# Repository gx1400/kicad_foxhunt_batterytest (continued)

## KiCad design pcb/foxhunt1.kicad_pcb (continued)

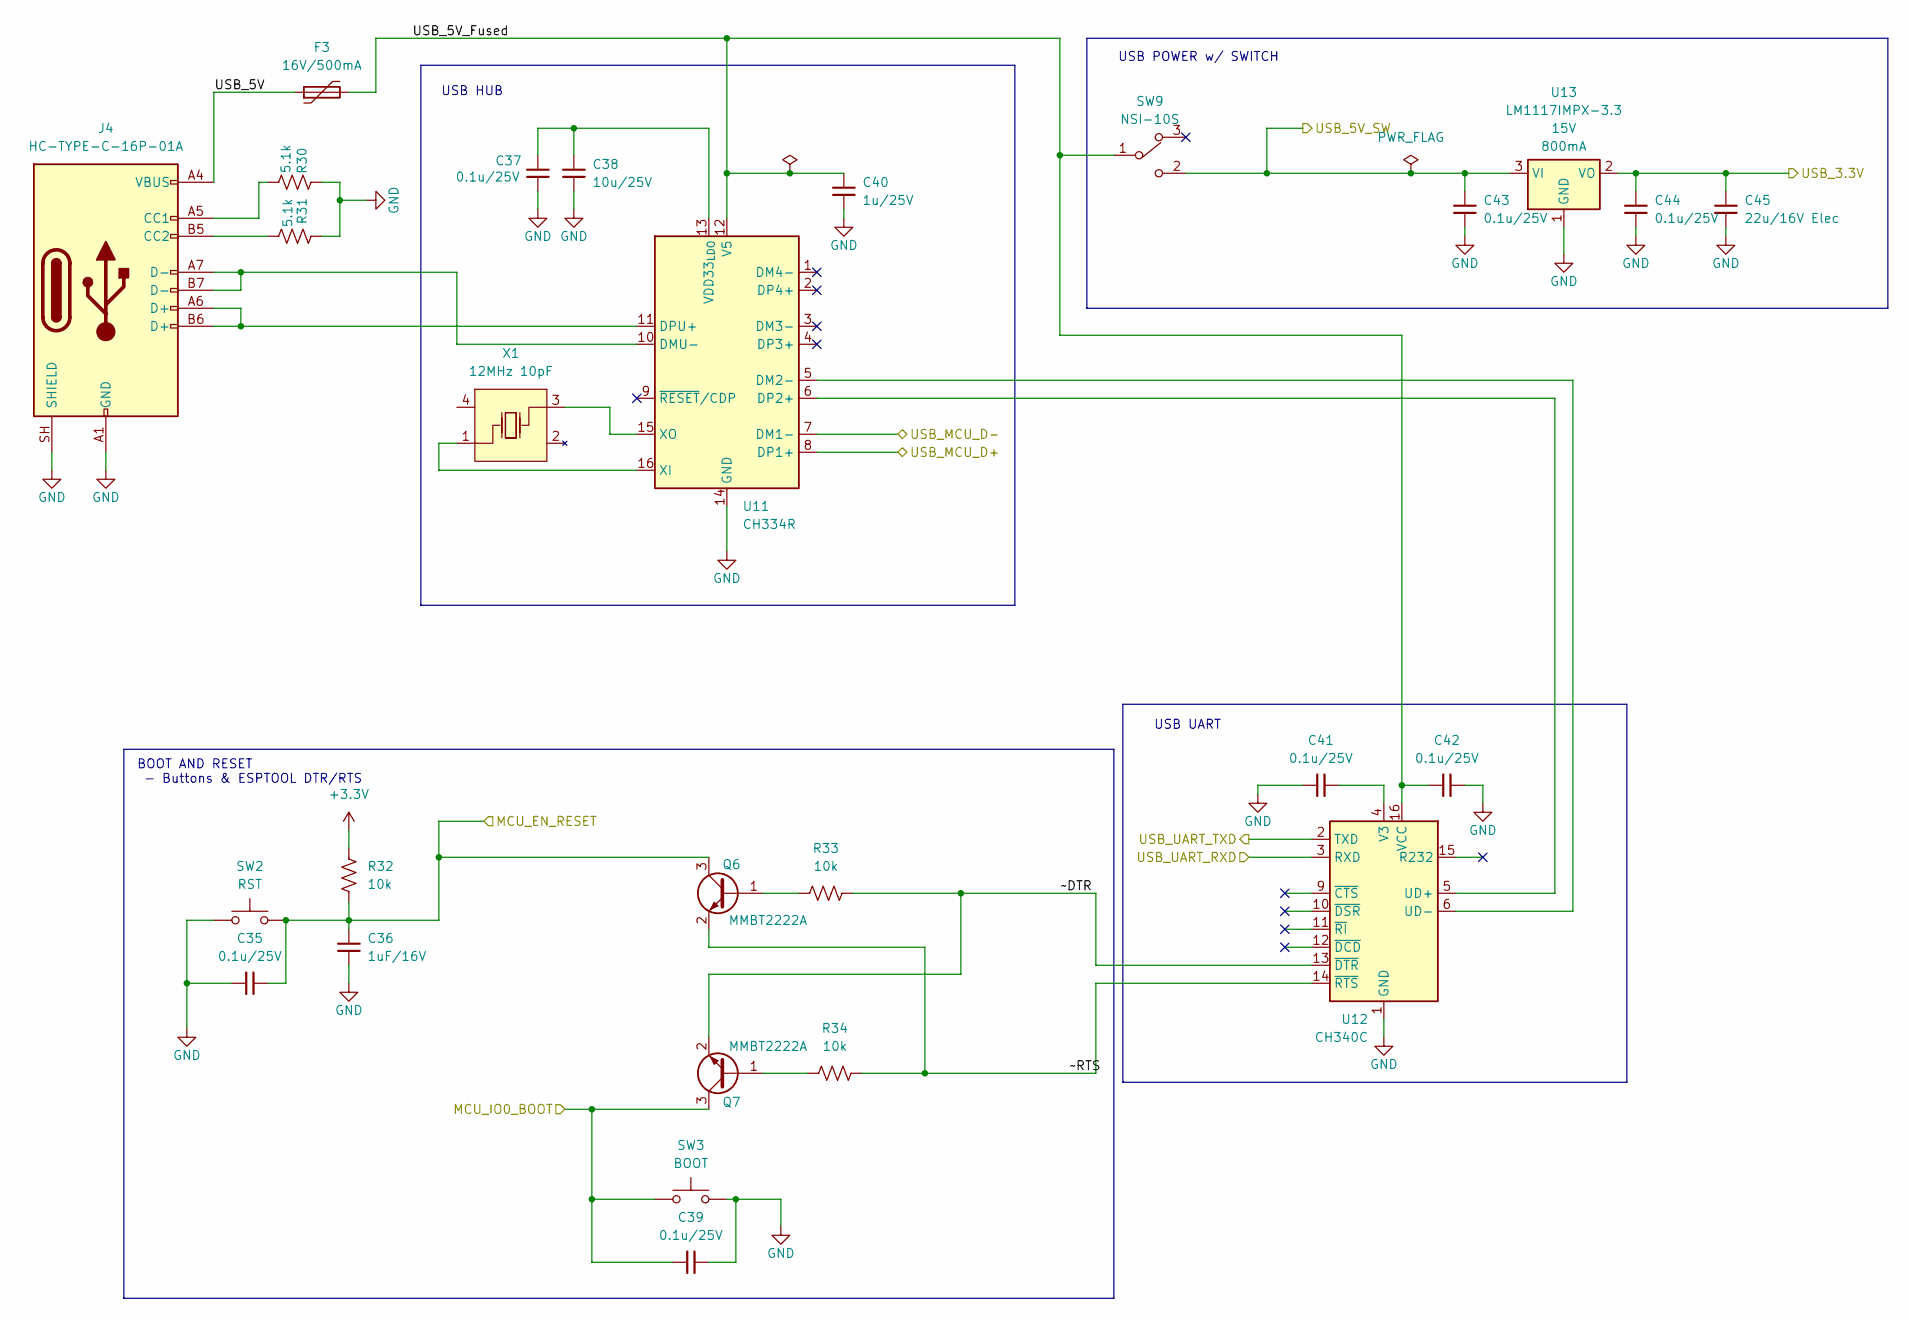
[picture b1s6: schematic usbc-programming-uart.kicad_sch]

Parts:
C35, C37, C39, C41, C42, C43, C44: 0.1u/25V; C_0603_1608Metric; MPN GRM188R71H104KA93D; LCSC Part # C77055
C36: 1uF/16V; C_0805_2012Metric; MPN GRM21BR71H105KA12L; LCSC Part # C77083
C38: 10u/25V; C_0805_2012Metric; MPN GRM21BZ71E106KE15L; LCSC Part # C237493
C40: 1u/25V; C_0805_2012Metric; MPN GRM21BR71H105KA12L; LCSC Part # C77083
C45: 22u/16V Elec; C_Elec_5x5.8; MPN XT1C220M0506; LCSC Part # C5260805
F3: 16V/500mA; Fuse_0805_2012Metric; MPN 0805L050/16XR; LCSC Part # C22435898
J4: HC-TYPE-C-16P-01A; USB_C_Receptacle_HCTL_HC-TYPE-C-16P-01A; MPN HC-TYPE-C-16P-01A; LCSC Part # C2894897
Q6, Q7: MMBT2222A; SOT-23; MPN MMBT2222ALT1G; LCSC Part # C82460
R30, R31: 5.1k; R_0603_1608Metric; MPN RC0603JR-075K1L; LCSC Part # C14677
R32, R33, R34: 10k; R_0603_1608Metric; MPN RT0603BRD0710KL; LCSC Part # C95204
SW2: RST; SW_SPST_PTS645Sx43SMTR92; MPN K2-1102SP-A4SC-04; LCSC Part # C83916
SW3: BOOT; SW_SPST_PTS645Sx43SMTR92; MPN K2-1102SP-A4SC-04; LCSC Part # C83916
SW9: NSI-10S; SW-SMD_NSI-10S; MPN NSI-10S; LCSC Part C515802
U11: CH334R; QSOP-16_3.9x4.9mm_P0.635mm; MPN CH334R; LCSC Part # C4154405
U12: CH340C; SOIC-16_3.9x9.9mm_P1.27mm; MPN CH340C; LCSC Part # C84681
U13: LM1117IMPX-3.3; SOT-223-3_TabPin2; MPN LM1117IMPX-3.3/NOPB; LCSC Part # C23984
X1: 12MHz 10pF; CRYSTAL-SMD_4P-L2.5-W2.0-BL; MPN TXM12M0004252DBCEO00T; LCSC Part # C284154

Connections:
+3.3V: R32.2; also elsewhere on the board
/Power/USB_3.3V_IN: C44.1, C45.1, U13.2 (VO); also elsewhere on the board
/Power/USB_5V_SW: C43.1, SW9.2, U13.3 (VI); also elsewhere on the board
/USB-C/MCU_EN_RESET: C35.1, C36.1, Q6.3 (C), R32.1, SW2.2; also elsewhere on the board
/USB-C/MCU_IO0_BOOT: C39.1, Q7.3 (C), SW3.2; also elsewhere on the board
/USB-C/USB_5V: F3.1, J4.A4 (VBUS), J4.A9 (VBUS), J4.B4 (VBUS), J4.B9 (VBUS)
/USB-C/USB_5V_Fused: C40.1, C42.1, F3.2, SW9.1, U11.12 (V5), U12.16 (VCC)
/USB-C/USB_MCU_D+: U11.8 (DP1+); also elsewhere on the board
/USB-C/USB_MCU_D-: U11.7 (DM1-); also elsewhere on the board
/USB-C/USB_UART_RXD: U12.3 (RXD); also elsewhere on the board
/USB-C/USB_UART_TXD: U12.2 (TXD); also elsewhere on the board
/USB-C/~DTR: Q7.2 (E), R33.1, U12.13 (~DTR)
/USB-C/~RTS: Q6.2 (E), R34.1, U12.14 (~RTS)
GND: C35.2, C36.2, C37.2, C38.2, C39.2, C40.2, C41.1, C42.2, C43.2, C44.2, C45.2, J4.A1 (GND), J4.A12 (GND), J4.B1 (GND), J4.B12 (GND), J4.SH (SHIELD), R30.1, R31.1, SW2.1, SW3.1, U11.14 (GND), U12.1 (GND), U13.1 (GND); also elsewhere on the board
unnamed: J4.A5 (CC1), R30.2
unnamed: J4.B5 (CC2), R31.2
unnamed: Q6.1 (B), R33.2
unnamed: Q7.1 (B), R34.2
unnamed: U11.5 (DM2-), U12.6 (UD-)
unnamed: J4.A7 (D-), J4.B7 (D-), U11.10 (DMU-)
unnamed: U11.6 (DP2+), U12.5 (UD+)
unnamed: J4.A6 (D+), J4.B6 (D+), U11.11 (DPU+)
unnamed: C37.1, C38.1, U11.13 (VDD33_{LDO})
unnamed: U11.16 (XI), X1.1
unnamed: U11.15 (XO), X1.3
unnamed: C41.2, U12.4 (V3)

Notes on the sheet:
USB UART
BOOT AND RESET - Buttons & ESPTOOL DTR/RTS
USB HUB
USB POWER w/ SWITCH

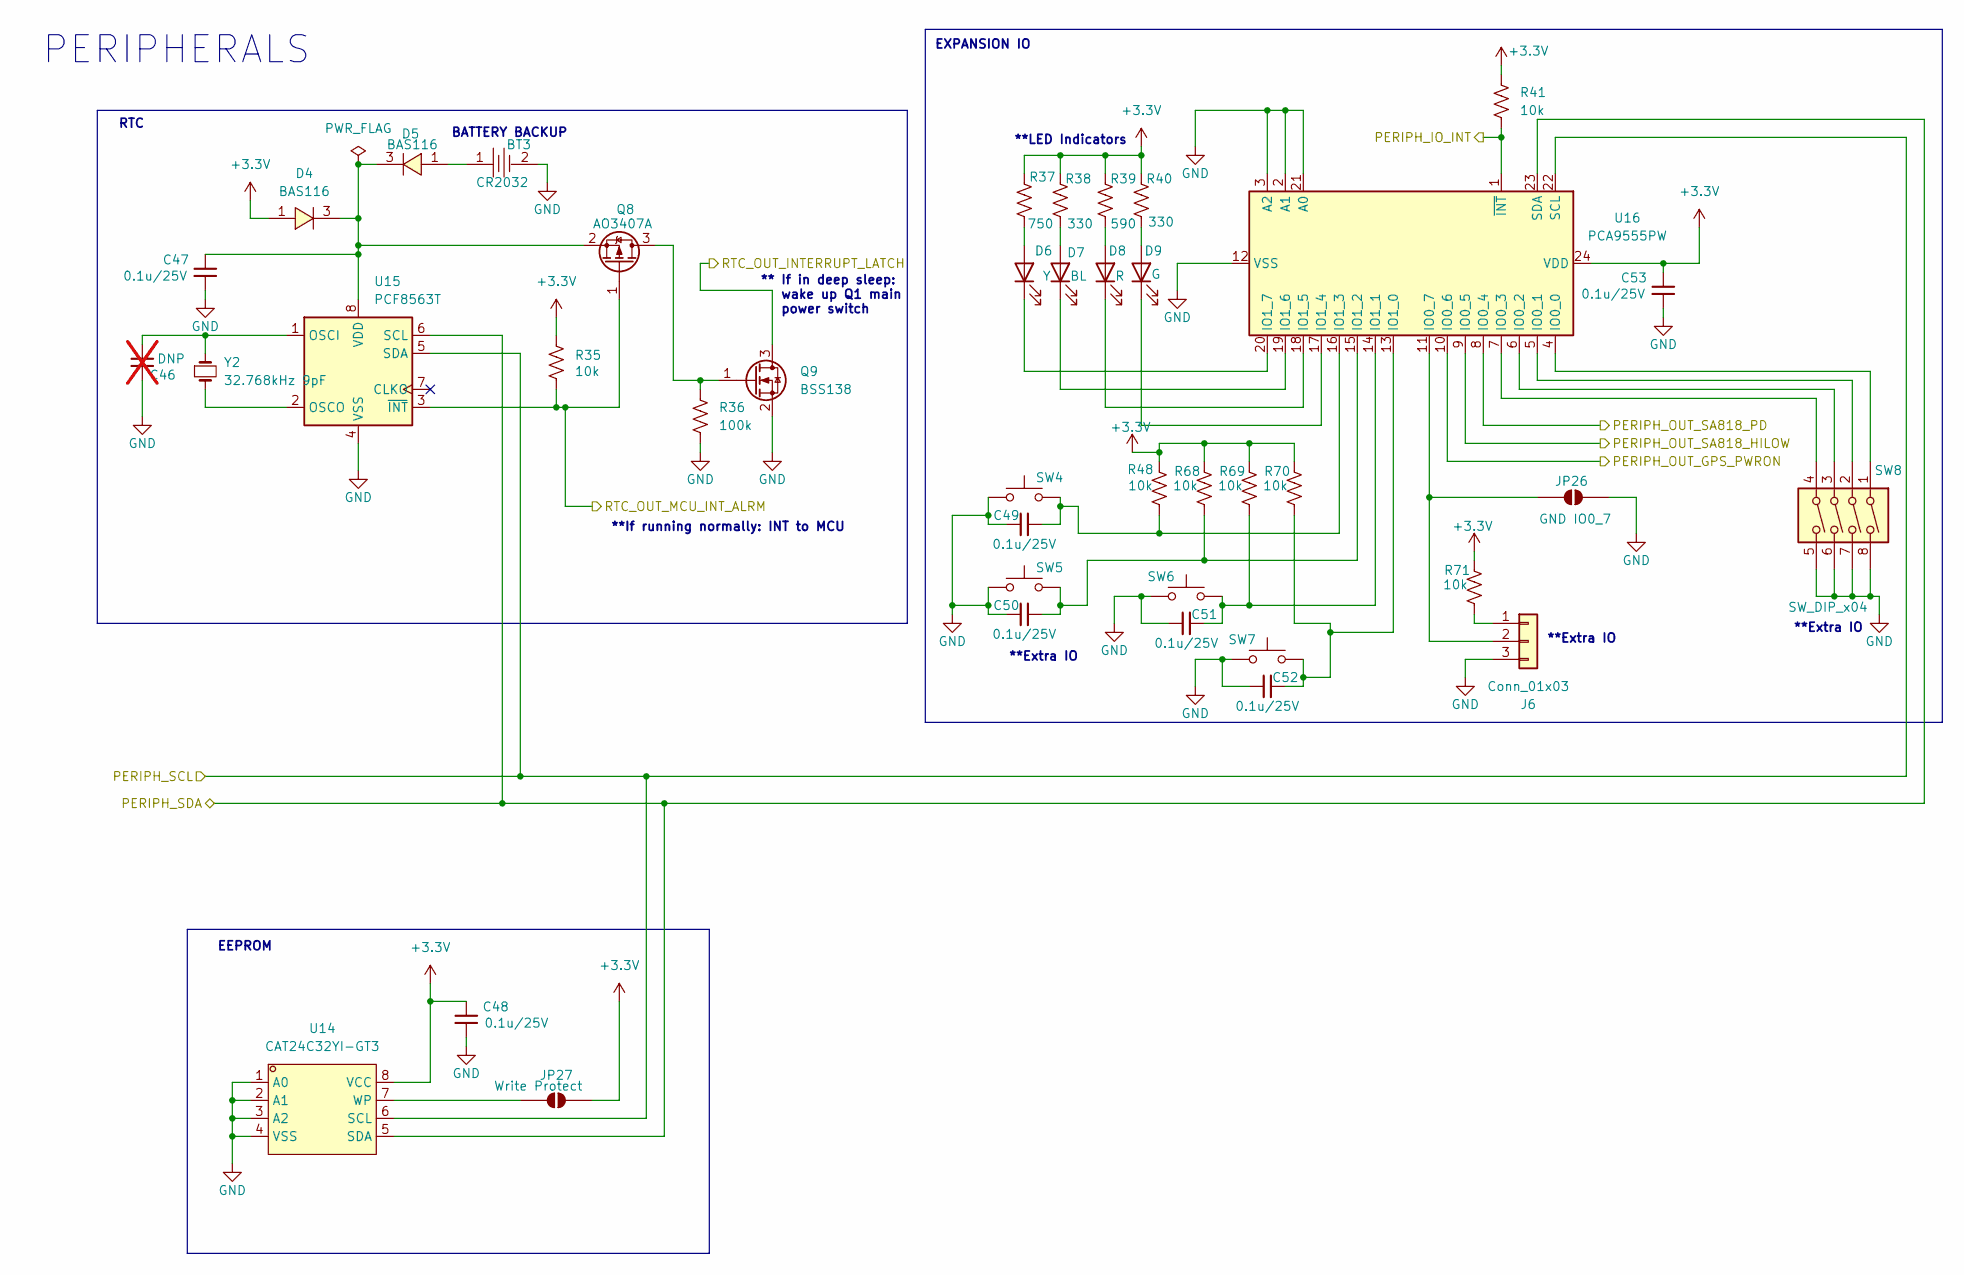
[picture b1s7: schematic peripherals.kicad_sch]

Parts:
BT3: CR2032; BAT-SMD_BS-08-B2AA016; MPN BS-08-B2AA020-R; LCSC Part C964787
C46: DNP; C_0603_1608Metric; not fitted
C47, C48, C49, C50, C51, C52, C53: 0.1u/25V; C_0603_1608Metric; MPN GRM188R71H104KA93D; LCSC Part # C77055
D4, D5: BAS116; SOT-23_L2.9-W1.3-P1.90-LS2.4-BR; MPN BAS116LT1G; LCSC Part # C232527
D6: Y; LED_0805_2012Metric; MPN APTD2012LSYCK; LCSC Part # C5588998
D7: BL; LED_0805_2012Metric; MPN APTD2012LQBC/D; LCSC Part # C5879058
D8: R; LED_0805_2012Metric; MPN APTD2012LSURCK; LCSC Part # C5366382
D9: G; LED_0805_2012Metric; MPN APT2012LZGCK; LCSC Part # C5569446
J6: Conn_01x03; JST_PH_B3B-PH-SM4-TB_1x03-1MP_P2.00mm_Vertical; MPN B3B-PH-SM4-TB(LF)(SN); LCSC Part # C160353
JP26: GND IO0_7; SolderJumper-2_P1.3mm_Open_TrianglePad1.0x1.5mm
JP27: Write Protect; SolderJumper-2_P1.3mm_Open_TrianglePad1.0x1.5mm
Q8: AO3407A; SOT-23; MPN AO3407A; LCSC Part # C15155
Q9: BSS138; SOT-23
R35, R41, R48, R68, R69, R70, R71: 10k; R_0603_1608Metric; MPN RT0603BRD0710KL; LCSC Part # C95204
R36: 100k; R_0603_1608Metric; MPN RC0603FR-07100KL; LCSC Part # C14675
R37: 750; R_0603_1608Metric; MPN RC0603FR-07750RL; LCSC Part # C114635
R38, R40: 330; R_0603_1608Metric; MPN RC0603FR-07330RL; LCSC Part # C105881
R39: 590; R_0603_1608Metric; MPN RC0603DR-07590RL; LCSC Part # C859077
SW4, SW5, SW6, SW7: GENERAL; SW_SPST_PTS645Sx43SMTR92; MPN K2-1102SP-A4SC-04; LCSC Part # C83916
SW8: SW_DIP_x04; SW_DIP_SPSTx04_Slide_KingTek_DSHP04TS_W7.62mm_P1.27mm; MPN DSHP04TS-S; LCSC Part # C319050
U14: CAT24C32YI-GT3; TSSOP-8_L4.4-W3.0-P0.65-LS6.4-BL; MPN CAT24C32YI-GT3; LCSC Part # C94264
U15: PCF8563T; SOIC-8_3.9x4.9mm_P1.27mm; MPN PCF8563T/5,518; LCSC Part # C7440
U16: PCA9555PW; TSSOP-24_4.4x7.8mm_P0.65mm; MPN PCA9555PWR; LCSC Part # C2864778
Y2: 32.768kHz 9pF; Crystal_SMD_3215-2Pin_3.2x1.5mm; MPN NX3215SA-32.768K-STD-MUA-9; LCSC Part # C519280

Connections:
+3.3V: C48.1, C53.1, D4.1, JP27.2 (B), R35.2, R37.1, R38.2, R39.1, R40.1, R41.2, R48.1, R68.1, R69.1, R70.1, R71.1, U14.8 (VCC), U16.24 (VDD); also elsewhere on the board
/GPS/GPS_IN_PWRON: U16.10 (IO0_6); also elsewhere on the board
/Peripherals/PERIPH_IO_INT: R41.1, U16.1 (~INT); also elsewhere on the board
/Peripherals/PERIPH_OUT_SA818_HILOW: U16.9 (IO0_5); also elsewhere on the board
/Peripherals/PERIPH_OUT_SA818_PD: U16.8 (IO0_4); also elsewhere on the board
/Peripherals/PERIPH_SCL: U14.6 (SCL), U15.5 (SDA), U16.22 (SCL); also elsewhere on the board
/Peripherals/PERIPH_SDA: U14.5 (SDA), U15.6 (SCL), U16.23 (SDA); also elsewhere on the board
/Peripherals/RTC_OUT_INTERRUPT_LATCH: Q9.3 (D); also elsewhere on the board
/Peripherals/RTC_OUT_MCU_INT_ALRM: Q8.1 (G), R35.1, U15.3 (~INT); also elsewhere on the board
GND: BT3.2, C46.1, C47.2, C48.2, C49.1, C50.1, C51.2, C52.2, C53.2, J6.3, JP26.2 (B), Q9.2 (S), R36.1, SW4.2, SW5.2, SW6.1, SW7.1, SW8.5, SW8.6, SW8.7, SW8.8, U14.1 (A0), U14.2 (A1), U14.3 (A2), U14.4 (VSS), U15.4 (VSS), U16.2 (A1), U16.3 (A2), U16.12 (VSS), U16.21 (A0); also elsewhere on the board
unnamed: BT3.1, D5.1
unnamed: D6.2 (A), R37.2
unnamed: D6.1 (K), U16.20 (IO1_7)
unnamed: D7.2 (A), R38.1
unnamed: D7.1 (K), U16.19 (IO1_6)
unnamed: D8.2 (A), R39.2
unnamed: D8.1 (K), U16.18 (IO1_5)
unnamed: D9.2 (A), R40.2
unnamed: D9.1 (K), U16.17 (IO1_4)
unnamed: J6.1, R71.2
unnamed: J6.2, JP26.1 (A), U16.11 (IO0_7)
unnamed: JP27.1 (A), U14.7 (WP)
unnamed: Q8.3 (D), Q9.1 (G), R36.2
unnamed: C47.1, D4.3, D5.3, Q8.2 (S), U15.8 (VDD)
unnamed: C46.2, U15.1 (OSCI), Y2.1
unnamed: U15.2 (OSCO), Y2.2
unnamed: SW8.1, U16.4 (IO0_0)
unnamed: SW8.2, U16.5 (IO0_1)
unnamed: SW8.3, U16.6 (IO0_2)
unnamed: SW8.4, U16.7 (IO0_3)
unnamed: C52.1, R70.2, SW7.2, U16.13 (IO1_0)
unnamed: C51.1, R69.2, SW6.2, U16.14 (IO1_1)
unnamed: C50.2, R68.2, SW5.1, U16.15 (IO1_2)
unnamed: C49.2, R48.2, SW4.1, U16.16 (IO1_3)

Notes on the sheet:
BATTERY BACKUP
**Extra IO
** If in deep sleep: wake up Q1 main power switch
EEPROM
**If running normally: INT to MCU
**LED Indicators
PERIPHERALS
RTC
EXPANSION IO

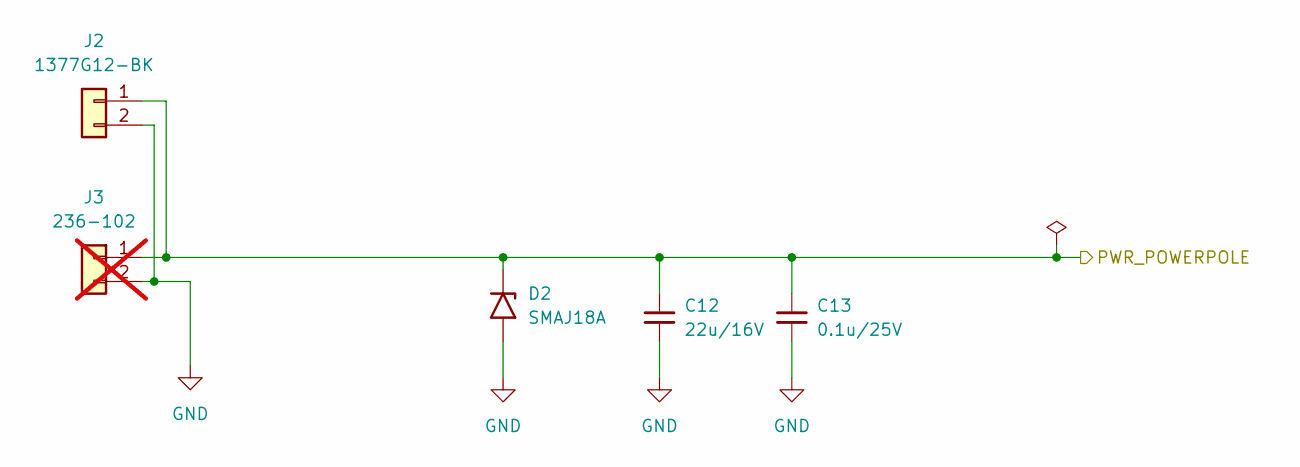
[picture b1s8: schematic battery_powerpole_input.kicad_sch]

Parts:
C12: 22u/16V; C_1206_3216Metric; MPN GRM31CZ71C226ME15L; LCSC Part # C909845
C13: 0.1u/25V; C_0603_1608Metric; MPN GRM188R71H104KA93D; LCSC Part # C77055
D2: SMAJ18A; D_SMA; MPN SMAJ18A; LCSC Part # C148219
J2: 1377G12-BK; Connector_Anderson_PP25_RA_1377g12-bk; MPN 1377G12-BK; Digikey PN 2243-1377G12-BK-ND
J3: 236-102; TerminalBlock_WAGO_236-102_1x02_P5.00mm_45Degree; MPN 236-102; not fitted

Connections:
/Power/Battery_PowerPole_Input/PWR_POWERPOLE: C12.1, C13.1, D2.1 (A1), J2.1, J3.1; also elsewhere on the board
GND: C12.2, C13.2, D2.2 (A2), J2.2, J3.2; also elsewhere on the board

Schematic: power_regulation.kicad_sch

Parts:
C14, C15, C20, C21, C26, C27, C28, C29: 0.1u/25V; C_0603_1608Metric; MPN GRM188R71H104KA93D; LCSC Part # C77055
C16, C17, C18, C19: 10u/25V; C_0603_1608Metric; MPN GRM188R61E106KA73D; LCSC Part # C344022
C22, C23, C24, C25: 22u/16V; C_1206_3216Metric; MPN GRM31CZ71C226ME15L; LCSC Part # C909845
C30, C31: 22u/16V Elec; C_Elec_5x5.8; MPN XT1C220M0506; LCSC Part # C5260805
JP12, JP14, JP16, JP18, JP22, JP24: Jumper_2_Open; TestPoint_2Pads_Pitch2.54mm_Drill0.8mm
JP20: 5V TEST LOAD; TestPoint_2Pads_Pitch2.54mm_Drill0.8mm
JP21: 3.3V TEST LOAD; TestPoint_2Pads_Pitch2.54mm_Drill0.8mm
L1, L2: 3.3uH; L_Chilisin_MHCI06030; MPN MHCI06030-3R3M-R8; LCSC Part # C108294
R18, R19, R20, R21: 10k; R_0603_1608Metric; MPN RT0603BRD0710KL; LCSC Part # C95204
R22: 76.8k; R_0603_1608Metric; MPN RT0603BRD0776K8L; LCSC Part # C705795
R23: 52.3k; R_0603_1608Metric; MPN RT0603BRD0752K3L; LCSC Part # C861462
R24: 24.9 2W; R_Axial_Power_L20.0mm_W6.4mm_P5.08mm_Vertical; not fitted
R25: 16.5 2W; R_Axial_Power_L20.0mm_W6.4mm_P5.08mm_Vertical; not fitted
U6, U7: TPS563201; SOT-23-6; MPN TPS563201DDCR; LCSC Part # C116592
U8: LM1085-5.0; TO-263-3_TabPin2; MPN LM1085IS-5.0RG; LCSC Part # C2865978
U9: LM1117IMPX-3.3; SOT-223-3_TabPin2; MPN LM1117IMPX-3.3/NOPB; LCSC Part # C23984

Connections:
/Power/Power Regulation/3V3_BUCK_OUT: C23.1, C25.1, JP18.1 (A), L2.2, R23.1
/Power/Power Regulation/3V3_BUCK_VIN: C15.1, C17.1, C19.1, JP14.2 (B), R19.2, U7.3 (VIN)
/Power/Power Regulation/3V3_LDO_OUT: C29.1, C31.1, JP21.2 (B), JP24.1 (A), U9.2 (VO)
/Power/Power Regulation/3V3_LDO_VIN: C27.1, JP18.2 (B), U9.3 (VI)
/Power/Power Regulation/4.8V_Intermediate: C21.1, L2.1, U7.2 (SW)
/Power/Power Regulation/5V_BUCK_OUT: C22.1, C24.1, JP16.1 (A), L1.2, R22.1
/Power/Power Regulation/5V_BUCK_VIN: C14.1, C16.1, C18.1, JP12.2 (B), R18.2, U6.3 (VIN)
/Power/Power Regulation/5V_LDO_OUT: C28.1, C30.1, JP20.2 (B), JP22.1 (A), U8.2 (VO)
/Power/Power Regulation/5V_LDO_VIN: C26.1, JP16.2 (B), U8.3 (VI)
/Power/Power Regulation/6V_intermediate: C20.1, L1.1, U6.2 (SW)
/Power/Power Regulation/BATT_3.3V_REG: JP24.2 (B); also elsewhere on the board
/Power/Power Regulation/BATT_5V_REG: JP22.2 (B); also elsewhere on the board
/Power/VRAW_GATED: JP12.1 (A), JP14.1 (A); also elsewhere on the board
GND: C14.2, C15.2, C16.2, C17.2, C18.2, C19.2, C22.2, C23.2, C24.2, C25.2, C26.2, C27.2, C28.2, C29.2, C30.2, C31.2, R20.1, R21.1, R24.2, R25.2, U6.1 (GND), U7.1 (GND), U8.1 (GND), U9.1 (GND); also elsewhere on the board
unnamed: JP20.1 (A), R24.1
unnamed: JP21.1 (A), R25.1
unnamed: R18.1, U6.5 (EN)
unnamed: C20.2, U6.6 (VBST)
unnamed: R20.2, R22.2, U6.4 (VFB)
unnamed: R19.1, U7.5 (EN)
unnamed: C21.2, U7.6 (VBST)
unnamed: R21.2, R23.2, U7.4 (VFB)

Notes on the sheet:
6V Intermediate Power
(Ref C1)
(Ref R1)
4.78V Intermediate Power
(Ref R2)
Vout = 0.768 (1 + R1/R2) <= R2=10k 4.7 = 0.768(1+R1/10k) => R1 = 51.2k => 52.3k => R2 = 10k = 4.78V L = 3.3uH typ from Table 7-2
6.6V Calculations ----------------
(Ref C9)
7.4V Nominal for 2x 18650 12-14V Nominal for Anderson Powerpole
5V rail: Buck pre-regulator: TPS563201 (4.5-17V in, 2A, synchronous), set to ~6V @ 2A intermediate output LDO cleanup stage: LM1085-5.0 (fixed 5V, 3A rated, ~1V dropout at 2A), taking the 6V intermediate down to a clean 5V
(Ref C2)
(Ref C8)
Icorms = (Vout * (Vin - Vout)) / (sqrt(12) * Vin * Lo * fsw) = 6.6 * (14.4 - 6.6) / (3.464 * 14.4 * 3.3e-6 * 588e3) = 0.531A
**6.6V**
4.7V Calculations ----------------
(Ref C3)
(Ref C7)
fsw = 588kHz from Section 5-5 or ~600kHz from Tables 5-6 IIp-p = (Vout/Vinmax) * ((Vinmax - Vout) / (Lo * fSw)) = (6.6/14.4) * ((14.4 -6.6) / (3.3e-6 * 588e3)) = 0.458 * (7.8 / 1.9404) = 1.84A IIpk = Io + IIp-p/2 = 2 + (1.84/2) = 2.92A ILO = sqrt(Io^2 + (1/12)(IIp-p)^2) = 2.07
Vout = 0.768 (1 + R1/R2) <= R2=10k 6.6 = 0.768(1+R1/10k) => R1 = 76k -> 76.8k => R2 = 10k L = 3.3uH typ from Table 7-2
3.3V rail: Buck pre-regulator: second TPS563201, set to ~4.3V @ 1A intermediate output LDO cleanup stage: LM1085-3.3 (fixed 3.3V, 3A rated), taking the 4.3V intermediate down to a clean 3.3V
**4.78V**

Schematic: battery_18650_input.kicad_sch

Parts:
BT1, BT2: Battery_Cell; BatteryHolder_MPD_BH-18650-PC; MPN BH-18650-PC; LCSC Part # C5339083; not fitted
C6, C7: 0.1u/25V; C_0603_1608Metric; MPN GRM188R71H104KA93D; LCSC Part # C77055
C8: 0.47u/25V; C_0805_2012Metric; MPN GCM219R71E474KA55D; LCSC Part # C437481
C9, C10, C11: 0.47u/10V; C_0603_1608Metric; MPN GRM188R71A474KA61D; LCSC Part # C435402
F1: CLM1612P1412; Fuse_PTCC_CLM1612; MPN CLM1612P1412; LCSC Part # C5353611
Q2: AO3400A; SOT-23; MPN AO3400A; LCSC Part # C20917
Q3: 8205A; SOT23-6L; MPN 8205A; LCSC Part # C22458966
R12: 10; R_0805_2012Metric; MPN RC0805FR-0710RL; LCSC Part # C96347
R13, R14: 150; R_1206_3216Metric; MPN RT1206BRD07150RL; LCSC Part # C870430
R15: 0.0025; RES-SMD_L6.4-W3.2-R2512_Sense4Pin; MPN HoJLR2512-3W-2.5mR-1%; LCSC Part # C2904234
R16: 1k; R_0805_2012Metric; MPN RC0805FR-071KL; LCSC Part # C95781
R17: 820; R_0805_2012Metric; MPN RC0805FR-07820RL; LCSC Part # C114544
TH1: NCP15XH103F03RC; R_0402_1005Metric; MPN NCP15XH103F03RC; LCSC Part # C77131
U5: MAX17320; TQFN-24-1EP_4x4mm_P0.5mm_EP2.1x2.1mm; MPN MAX17320G22+; LCSC Part # C2914309

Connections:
/Peripherals/PERIPH_SCL: U5.8 (SCL/OD); also elsewhere on the board
/Peripherals/PERIPH_SDA: U5.9 (SDA/DQ); also elsewhere on the board
/Power/BMS_ALRT: U5.7 (ALRT); also elsewhere on the board
/Power/Battery 18650 Input/BATT+: BT1.1 (+), F1.1, R12.1, R13.1
/Power/Battery 18650 Input/BATT_Plus_to_Minus: BT1.2 (-), BT2.1 (+), R14.1
/Power/Battery 18650 Input/PWR_18650: Q3.3 (S2), R16.2, R17.2; also elsewhere on the board
/Power/Battery 18650 Input/PolyFuseOut: F1.3, Q3.1 (S1)
GND: R15.4; also elsewhere on the board
GNDREF: BT2.2 (-), C6.2, C7.2, C9.2, C10.2, C11.2, Q2.2 (S), R15.1, TH1.2, U5.20 (GND), U5.25 (GND)
unnamed: F1.2, Q2.3 (D)
unnamed: Q2.1 (G), U5.11 (PFAIL)
unnamed: Q3.6 (G1), U5.3 (CHG)
unnamed: Q3.4 (G2), U5.4 (DIS)
unnamed: C11.1, U5.12 (AOLDO)
unnamed: R13.2, U5.24 (BATTS)
unnamed: C6.1, R14.2, U5.21 (CELL1), U5.22 (CELL2), U5.23 (CELL3)
unnamed: C8.1, U5.2 (CP)
unnamed: R15.3, U5.14 (CSN)
unnamed: R15.2, U5.15 (CSP)
unnamed: C7.1, C8.2, R12.2, U5.1 (IN)
unnamed: R16.1, U5.6 (PCKP)
unnamed: C10.1, U5.17 (REG2)
unnamed: C9.1, U5.13 (REG3)
unnamed: TH1.1, U5.10 (TH1)
unnamed: R17.1, U5.5 (ZVC)

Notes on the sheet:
18650s
R13: intentional GND/GNDREF split for current sensing — do not bridge elsewhere
BATTS: RBAL4 => IBALMAX = VCELLMAX / (2 x RBAL+ RSWITCH) CELL1: RBAL1 => IBALMAX = VCELLMAX / (RBAL+ RSWITCH) RSWITCH = 9ohm typ VCELLMAX = 4.2V for 18650 IBALMAX = 100mA => 50mA RBAL1 = 150ohm IBALMAX = 26mA = 105mW = use 1/4W 0805 minimum

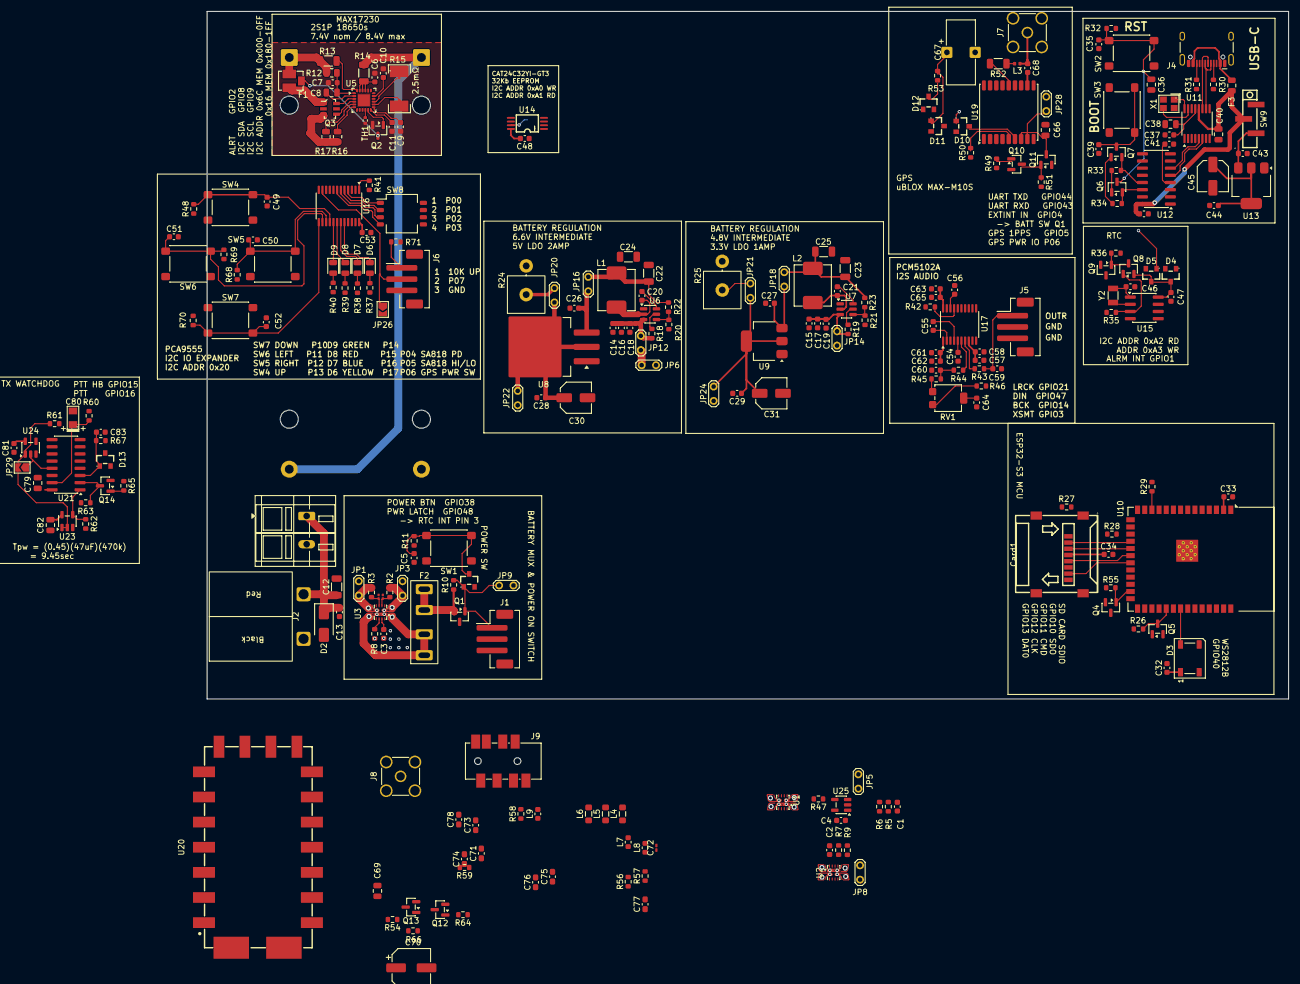
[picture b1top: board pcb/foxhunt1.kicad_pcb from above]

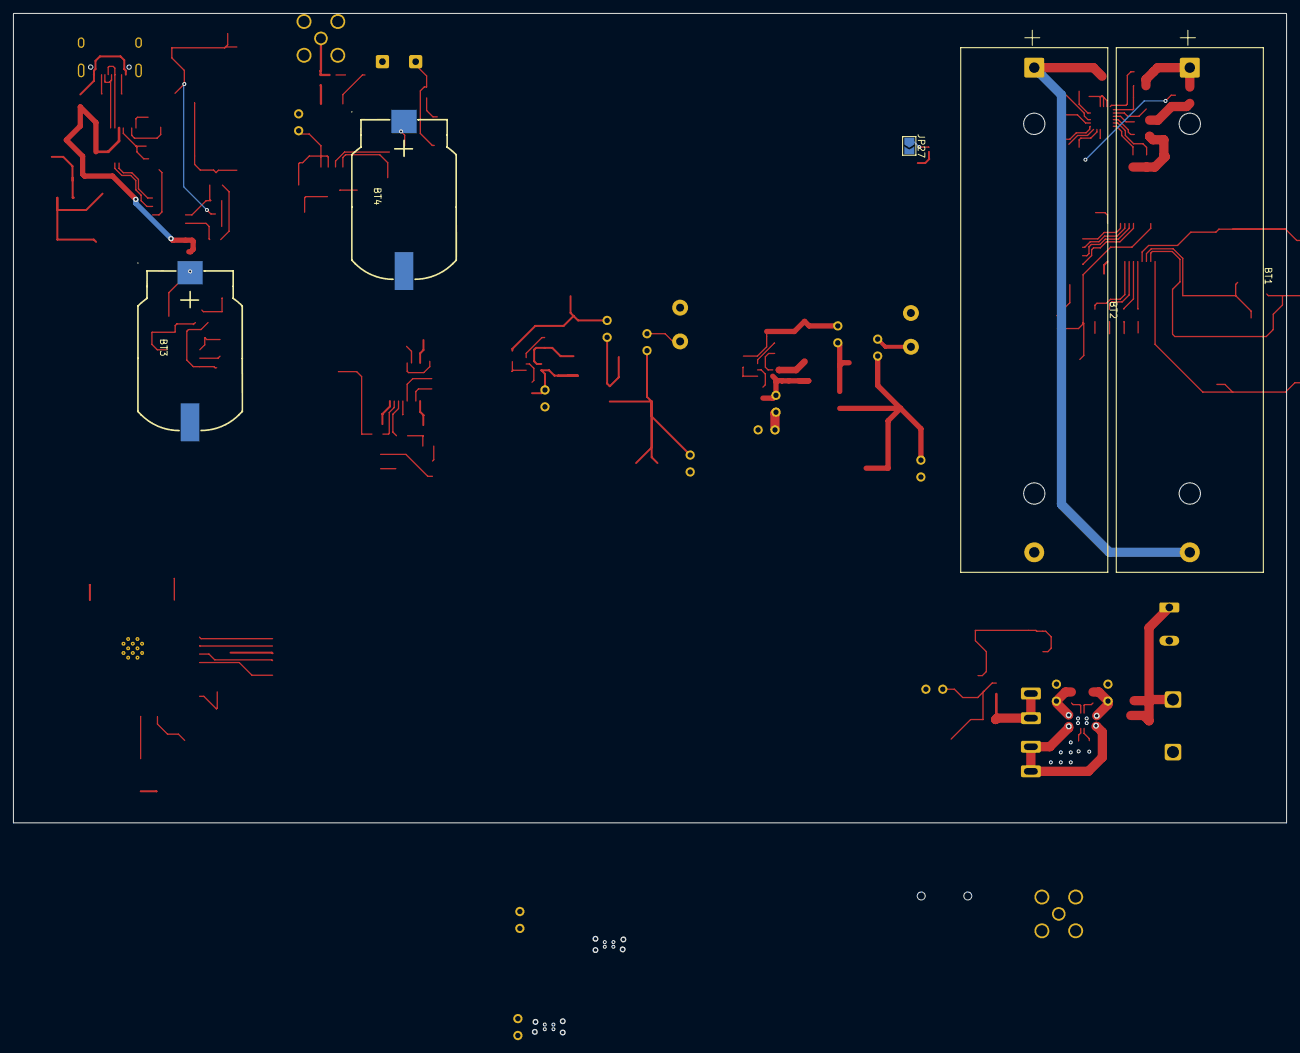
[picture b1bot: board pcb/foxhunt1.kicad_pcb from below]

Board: 4 copper layers, 191.5 x 121.8 mm, 260 parts (5 on the bottom side), 177 nets.

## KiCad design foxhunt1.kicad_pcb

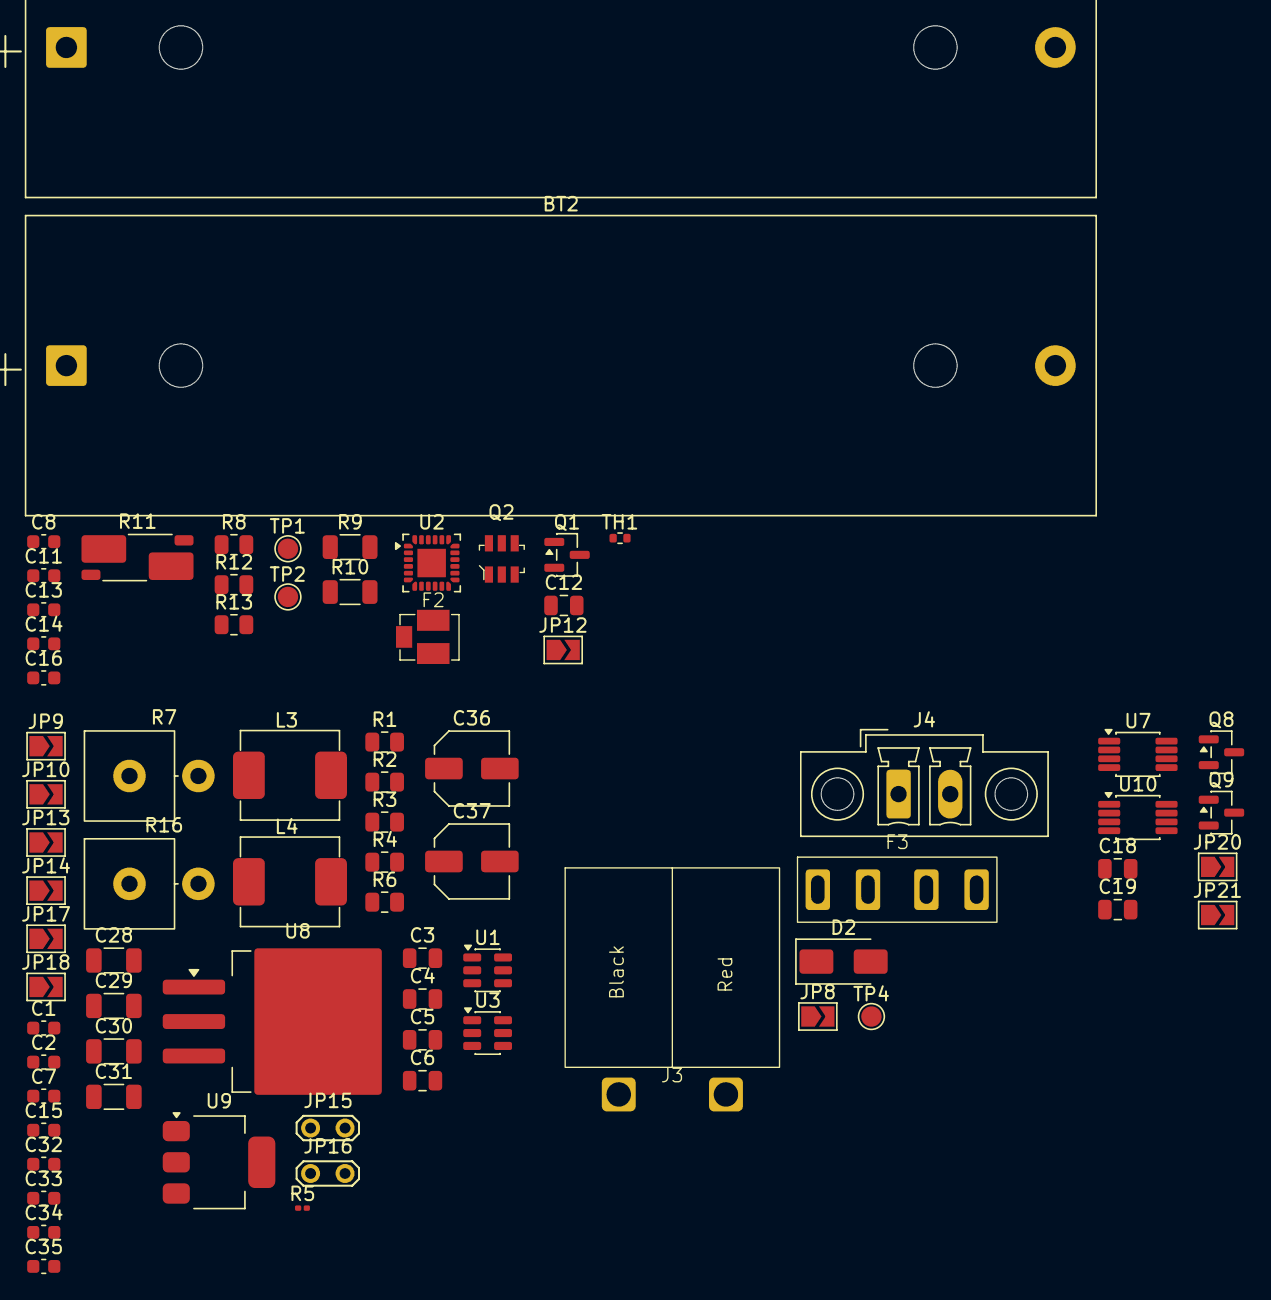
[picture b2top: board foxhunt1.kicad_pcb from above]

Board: 2 copper layers, 76 parts (0 on the bottom side), 53 nets, no tracks yet.

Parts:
BT1, BT2: Battery_Cell; BatteryHolder_MPD_BH-18650-PC
C1, C2, C7, C8, C11, C15, C32, C33, C34, C35: 0.1u/25V; C_0603_1608Metric
C3, C4, C5, C6: 10u/25V; C_0805_2012Metric
C12: 0.47u/25V; C_0805_2012Metric
C13, C14, C16: 0.47u/10V; C_0603_1608Metric
C18, C19: 1u/16V; C_0805_2012Metric
C28, C29, C30, C31: 22u/16V; C_1206_3216Metric
C36, C37: 22u/16V Elec; C_Elec_5x5.8
D2: SMAJ18A; D_SMA
F2: CLM1612P1412; Fuse_PTCC_CLM1612
F3: Fuse 2A; Fuse_MCCQ-122
J3: 1377G12-BK; Connector_Anderson_PP25_RA_1377g12-bk
J4: MCV 1,5/ 2-GF-3,81; PhoenixContact_MCV_1,5_2-GF-3.81_1x02_P3.81mm_Vertical_Thre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
JP8, JP9, JP10, JP12, JP13, JP14, JP17, JP18, JP20, JP21: SolderJumper_2_Open; SolderJumper-2_P1.3mm_Open_TrianglePad1.0x1.5mm
JP15, JP16: Jumper_2_Open; TestPoint_2Pads_Pitch2.54mm_Drill0.8mm
L3, L4: 3.3uH; L_Chilisin_MHCI06030
Q1, Q8, Q9: AO3400A; SOT-23
Q2: 8205A; SOT23-6L
R1, R2, R3, R4: 10k; R_0805_2012Metric
R5: 68.1k; R_0201_0603Metric
R6: 46.4k; R_0805_2012Metric
R7: 24.9 2W; R_Axial_Power_L20.0mm_W6.4mm_P5.08mm_Vertical
R8: 10; R_0805_2012Metric
R9, R10: 150; R_1206_3216Metric
R11: 0.0025; R_Shunt_Vishay_WSK2512_6332Metric_T2.21mm
R12: 1k; R_0805_2012Metric
R13: 820; R_0805_2012Metric
R16: 16.5 2W; R_Axial_Power_L20.0mm_W6.4mm_P5.08mm_Vertical
TH1: NCP15XH103F03RC; R_0402_1005Metric
TP1, TP2, TP4: TestPoint; TestPoint_Pad_D1.5mm
U1, U3: TPS563201; SOT-23-6
U2: TQFN-24-1EP_4x4mm_P0.5mm_EP2.1x2.1mm
U7, U10: LM74610; VSSOP-8_3x3mm_P0.65mm
U8: LM1085-5.0; TO-263-3_TabPin2
U9: AMS1117-3.3; SOT-223-3_TabPin2

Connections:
+12V: D2.1 (A1), F3.2, JP8.1 (A)
+BATT: BT1.1 (+), F2.1, R8.2, R9.2, TP2.1 (1_1)
/Battery 18650 Input/PWR_18650: JP12.2 (B), Q8.2 (S), U7.4 (ANODE)
/Battery_PowerPole_Input/PWR_POWERPOLE: JP8.2 (B), Q9.2 (S), U10.4 (ANODE)
/Power Regulation/PWR_IN_SELECT: JP9.1 (A), JP10.1 (A), JP20.2 (B), JP21.2 (B)
GND: C1.2, C2.2, C3.2, C4.2, C5.2, C6.2, C28.2, C29.2, C30.2, C31.2, C32.2, C33.2, C34.2, C35.2, C36.2, C37.2, D2.2 (A2), J3.2, J4.2, R3.2, R4.2, R7.1, R11.4, R16.1, U1.1 (GND), U3.1 (GND), U8.1 (GND), U9.1 (GND)
GNDREF: BT2.2 (-), C8.2, C11.2, C13.2, C14.2, C16.2, Q1.2 (S), R11.1, TH1.2, U2.20 (GND), U2.25 (GND)
unnamed: BT1.2 (-), BT2.1 (+), R10.2, TP1.1 (1_1)
unnamed: F3.1, J3.1, J4.1, TP4.1 (1_1)
unnamed: C1.1, C3.1, C5.1, JP9.2 (B), R1.1, U1.3 (VIN)
unnamed: C2.1, C4.1, C6.1, JP10.2 (B), R2.1, U3.3 (VIN)
unnamed: JP12.1 (A), Q2.3 (S2), R12.1, R13.1
unnamed: C28.1, C30.1, JP13.1 (A), L3.2, R5.2
unnamed: C32.1, JP13.2 (B), U8.3 (VI)
unnamed: C29.1, C31.1, JP14.1 (A), L4.2, R6.2
unnamed: C33.1, JP14.2 (B), U9.3 (VI)
unnamed: JP15.1 (A), R7.2
unnamed: C34.1, C36.1, JP15.2 (B), JP17.1 (A), U8.2 (VO)
unnamed: JP16.1 (A), R16.2
unnamed: C35.1, C37.1, JP16.2 (B), JP18.1 (A), U9.2 (VO)
unnamed: JP20.1 (A), Q8.3 (D), U7.8 (CATHODE)
unnamed: JP21.1 (A), Q9.3 (D), U10.8 (CATHODE)
unnamed: F2.2, Q1.3 (D)
unnamed: Q1.1 (G), U2.11 (PFAIL)
unnamed: Q2.6 (G1), U2.3 (CHG)
unnamed: Q2.4 (G2), U2.4 (DIS)
unnamed: F2.3, Q2.1 (S1)
unnamed: Q8.1 (G), U7.2 (GATE_DOWN), U7.6 (GATE_DRIVE)
unnamed: Q9.1 (G), U10.2 (GATE_DOWN), U10.6 (GATE_DRIVE)
unnamed: R1.2, U1.5 (EN)
unnamed: C7.1, L3.1, U1.2 (SW)
unnamed: C7.2, U1.6 (VBST)
unnamed: R3.1, R5.1, U1.4 (VFB)
unnamed: C16.1, U2.12 (AOLDO)
unnamed: R9.1, U2.24 (BATTS)
unnamed: C8.1, R10.1, U2.21 (CELL1), U2.22 (CELL2), U2.23 (CELL3)
unnamed: C12.1, U2.2 (CP)
unnamed: R11.3, U2.14 (CSN)
unnamed: R11.2, U2.15 (CSP)
unnamed: C11.1, C12.2, R8.1, U2.1 (IN)
unnamed: R12.2, U2.6 (PCKP)
unnamed: C14.1, U2.17 (REG2)
unnamed: C13.1, U2.13 (REG3)
unnamed: TH1.1, U2.10 (TH1)
unnamed: R13.2, U2.5 (ZVC)
unnamed: R2.2, U3.5 (EN)
unnamed: C15.1, L4.1, U3.2 (SW)
unnamed: C15.2, U3.6 (VBST)
unnamed: R4.1, R6.1, U3.4 (VFB)
unnamed: C18.1, U7.7 (VCAPH)
unnamed: C18.2, U7.1 (VCAPL)
unnamed: C19.1, U10.7 (VCAPH)
unnamed: C19.2, U10.1 (VCAPL)
